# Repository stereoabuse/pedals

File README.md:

# pedals

Guitar pedal boards by stereoabuse. Each folder is a complete, separate design: netlist, board, JLCPCB fabrication files, schematic, and build notes. None has been built yet.

| Design | What it is | Enclosure |
|---|---|---|
| [preamp](preamp/) | High-gain preamp with a boost built into its first stage | 1590BB |
| [boost-preamp](boost-preamp/) | Boost and high-gain preamp as two sections in series, for the band Manat | 1590BB |
| [screamer](screamer/) | One-knob overdrive: a Tube Screamer with Drive at zero and Level at maximum, Tone only | 1590B2 |
| [muff-screamer](muff-screamer/) | Black Russian Big Muff and TS808 Tube Screamer with a series / parallel / order toggle | 1590BB |
| [decade-drive](decade-drive/) | Drive with one Level knob and twenty three-way toggles, including a tunable feedback resonator | 1590XX |

All five run from a 9 V supply or a battery.

## The two preamps

Both are derived from the Friedman BE-OD circuit (via the public PedalPCB "Thermionic Distortion" schematic).

| | [preamp](preamp/) | [boost-preamp](boost-preamp/) |
|---|---|---|
| What it is | High-gain preamp with a boost built into its first stage | Boost and high-gain preamp as two sections in series, for the band Manat |
| Footswitches | Bypass, Boost (boost only works with the preamp on) | Preamp, Boost (each works on its own) |
| Knobs | Gain, Volume, Tight, Mid, Treble, Presence | Same |
| Toggles | Depth, Clip | Depth, Clip, Voice (boost voicing) |
| Boost | Up to +12 dB above 700 Hz | Unity to +21 dB, three voicings |
| Fab files | [preamp/fab](preamp/fab/) | [boost-preamp/fab](boost-preamp/fab/) |

| preamp | boost-preamp |
|---|---|
|  |  |

## screamer

## muff-screamer

Six knobs, two footswitches, one toggle. Unlike the others, its bypass is buffered rather than true bypass.

## decade-drive

No pots except Level. Each of the twenty toggles adds a fixed part when moved up or down from centre, in weighted steps like a decade resistance box, so every setting can be written down and repeated. One row is a feedback section that resonates, scoops or drones at a tuned pitch.

`tools/jlc.py` looks up JLCPCB part stock and prices and is shared by all of them. `tools/wiring.py` draws the wiring diagram in each design's `docs/` folder.

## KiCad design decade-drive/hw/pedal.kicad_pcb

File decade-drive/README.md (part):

# decade-drive

A drive pedal with one knob and twenty three-way toggles, by stereoabuse. The idea comes from a decade resistance box: instead of turning a pot, you add fixed, weighted parts with switches, so every setting is a pattern you can write down and get back to exactly. That includes the feedback section, which can sit just under, on, or over the edge of oscillation at a tuned pitch.

Commands below are run from inside this folder. Untested hardware: the circuit is simulated and the board passes KiCad DRC, but no board has been built yet. The Feedback and Chaos rows in particular are designed from simulation and will want adjusting by ear.

## How the toggles work

Every toggle is an SPDT on-off-on with its centre lug on a circuit node. Lever up connects one extra part to that node, lever down connects a different one, centre connects nothing. With all twenty centred the pedal is its plain "home" sound: a mid-gain overdrive with a 720 Hz bass cut, soft red-LED clipping and no feedback.

Where a row has toggles numbered 9, 3 and 1 (or 3 and 1), they do the same job with those weights, like the dials of a decade box: 9 is the coarse step, 1 the fine one, and they add up.

Seen from the front:

| Row | 1 | 2 | 3 | 4 | 5 |
|---|---|---|---|---|---|
| Drive | GAIN 9 | GAIN 3 | GAIN 1 | DIODE + | DIODE - |
| Shape | BASS 3 | BASS 1 | TREBLE 3 | TREBLE 1 | CLIP |
| Feedback | SIGN | AMOUNT 3 | AMOUNT 1 | PITCH 3 | PITCH 1 |
| Chaos | SAG | GATE | OCTAVE | BLEND | BURST |

Below the grid: Level knob (left), LED and bypass footswitch (centre).

## What each toggle does

Numbers are from the simulation (see below), not measurements.

| Toggle | Up | Centre (home) | Down |
|---|---|---|---|
| GAIN 9 | +15 dB | 0 dB | -15 dB |
| GAIN 3 | +9 dB | 0 dB | -9 dB |
| GAIN 1 | +4 dB | 0 dB | -4 dB |
| DIODE + | Silicon | Red LED | Schottky |
| DIODE - | Silicon | Red LED | Schottky |
| BASS 3, BASS 1 | More bass | 720 Hz cut | Less bass |
| TREBLE 3, TREBLE 1 | Brighter | 3.4 kHz roll-off | Darker |
| CLIP | Silicon hard clipper | Off | Schottky hard clipper |
| SIGN | Regenerative: resonance, then oscillation | No feedback | Degenerative: a scoop |
| AMOUNT 3, AMOUNT 1 | More feedback | | Less feedback |
| PITCH 3 | Octave up | D | Octave down |
| PITCH 1 | Up three semitones (F) | D | Down five (A) |
| SAG | Drive op-amp on about 6.3 V | Full supply | About 5.6 V |
| GATE | Gate | Off | Soft gate |
| OCTAVE | Octave up, into the drive | Off | Rectified signal into the mix |
| BLEND | Clean, in phase | Off | Clean, out of phase |
| BURST (momentary) | Drone burst while held | | Kill while held |

Gain steps add up to 18 dB either side of home. The gain stage sits before a fixed 23 dB drive stage, so total gain runs from about 5 to 42 dB.

DIODE + and DIODE - each pick the soft-clipping diode for one half of the wave, so mixed settings clip asymmetrically. For a 0.2 V peak-to-peak input at home gain the drive stage puts out about 2.0 V peak-to-peak on LEDs, 0.9 V on silicon and 0.35 V on Schottky, so expect to move the Level knob when you change diodes.

Bass corner in Hz (the frequency below which the drive stage is fed less signal):

| BASS 3 \ BASS 1 | up | centre | down |
|---|---|---|---|
| up | 72 | 92 | 135 |
| centre | 227 | 725 | 1065 |
| down | 560 | 1790 | 2130 |

Treble corner in Hz:

| TREBLE 3 \ TREBLE 1 | up | centre | down |
|---|---|---|---|
| up | 9400 | 7900 | 3900 |
| centre | 4900 | 3400 | 1700 |
| down | 1190 | 820 | 660 |

## The Feedback row

A band-pass filter (the resonator) listens to the drive stage's output, and SIGN decides what happens to what it hears.

- SIGN up feeds it back in phase. Below a loop gain of 1 this is a resonant peak at the resonator's pitch, like a parked wah. Above 1 the pedal oscillates at that pitch: a drone.
- SIGN down feeds it back out of phase, which takes a few dB out around that pitch. This path runs through the bass filter, so the scoop is deepest with BASS up (about 10 dB) and shallow with BASS down (about 3 dB).
- AMOUNT sets the loop gain. With the THRESH trimmer at mid travel the simulated values are:

| AMOUNT 3 \ AMOUNT 1 | up | centre | down |
|---|---|---|---|
| up | 1.51 | 1.44 | 1.14 |
| centre | 1.13 | 0.79 | 0.50 |
| down | 0.49 | 0.28 | 0.23 |

So at home AMOUNT the pedal is just under the edge (a 13 dB peak), and one click of AMOUNT 1 up tips it over. THRESH scales the whole table by roughly 0.6 to 2.8, which is how you put the edge exactly where you want it.

- PITCH sets the resonator. Home is D5 (587 Hz). The nine settings are the notes of a D minor chord over three octaves: A3, D4, F4, A4, D5, F5, A5, D6, F6 (220 Hz to 1.4 kHz). PITCH 3 moves by octaves, PITCH 1 picks D, F or A. The TUNE trimmer moves all nine together, from about A4 to F5 at the home setting, so the set can be retuned to another root within that range.
- BURST up forces a drone at the current pitch while held, whatever SIGN and AMOUNT are doing. BURST down mutes the output while held.

Three things worth knowing:

1. While you play, the note holds the drive stage and the drone stays out of the way. As the note decays the drone takes over. More gain keeps the note in charge for longer. This is the simulated behaviour for a single decaying note; chords and real pickups will be messier.
2. The loop gain does not change with the GAIN, BASS or TREBLE toggles. It does drop to roughly a third with Schottky diodes selected, because they leak across the drive stage.
3. The drone runs at the drive stage's clipping level, so at full Level it is loud (about 4 V peak-to-peak on LEDs).

### Setting the two trimmers

Both are on the SMD side, reachable with the back off.

1. TUNE: centre both PITCH toggles, hold BURST up, and adjust TUNE until a tuner on the output reads D. The BP test pad carries the resonator output if you would rather measure there.
2. THRESH: SIGN up, both AMOUNT toggles centred, nothing plugged in. Turn THRESH until the drone just stops. AMOUNT 1 up should then start it again.

The intervals between PITCH settings come from part ratios and should land within about a third of a semitone of each other. The absolute pitch depends on capacitor tolerance, which is what TUNE is for.

## The Chaos row

- SAG lowers the supply of the drive op-amp only. Up clips the positive half earlier; down leaves so little headroom that the positive half is cut off almost completely. What a TL072 really does this close to its limits is not in the simulation model, so treat this one as an experiment. Each SAG position draws about 20 to 25 mA extra. The octave rectifier shares that op-amp, so OCTAVE behaves differently while SAG is engaged.
- GATE subtracts a limited copy of the signal from itself after the clipper, which cancels anything small. Up is a full gate: anything under roughly 0.1 V peak-to-peak at that point is cut by 15 dB or more, so hiss and the tail of a note go. Down cancels half as much.
- OCTAVE up full-wave rectifies the signal before the drive stage, which doubles its frequency. Down adds the half-wave rectified clean signal to the output instead; with BLEND down as well the clean part becomes fully rectified.
- BLEND adds clean signal (after the gain stage) to the output, in or out of phase with the driven signal. With OCTAVE up, the in-phase clean signal is the rectified one.

## Ordering from JLCPCB

Files are in [fab/](fab/).

1. Upload `decade-drive-revA-gerbers.zip`. Settings: 4 layers, 1.6 mm, 94 x 99.5 mm. Layer order is F, In1, In2, B (`.gtl`, `.g1`, `.g2`, `.gbl`).
2. Turn on PCB Assembly, top side.
3. Upload `decade-drive-revA-bom.csv` and `decade-drive-revA-cpl.csv`.
4. In the placement preview, check pin 1 on U1 to U6, the MOSFET (Q1), the two trimmers (RV2, RV3), and the cathode marks on the diodes and the two red LEDs (LED2, LED3). JLC's rotation convention differs from KiCad's for some packages; the CPL applies the usual corrections for SOIC and SOT-23 parts only, so this is the step to catch a mistake.

49 BOM lines, 136 placements. 2 of the lines are JLC "extended" parts (a small one-time fee each): the 1 nF NP0 capacitor and the 100k trimmer. Stock was checked on 2026-11-22.

## Parts you solder

| Part | Qty | Notes |
|---|---|---|
| Mini toggle, SPDT on-off-on | 19 | Solder lug or PC pin, 4.7 mm lug pitch |
| Mini toggle, SPDT (on)-off-(on) momentary | 1 | BURST. Same size and pitch |
| Alpha 16 mm right-angle PCB pot (RV16AF-41) | 1 | A10K |
| 3PDT latching footswitch | 1 | Wired, not board mounted |
| 3 mm LED | 1 | Any colour |
| 1/4" jack | 2 | Input must be stereo (battery switching) |
| 2.1 mm DC jack with switch lug | 1 | Panel mount, insulated |
| 9V battery snap | 1 | |
| Hammond 1590XX enclosure | 1 | 145 x 121 x 39 mm |

Toggles, pot and LED mount on the back of the board (the side with the outlines). Fit them loosely, bolt everything into the drilled enclosure, then solder, so the heights settle correctly.

The toggles stand with their lugs in a vertical line, so the levers move up and down. As designed, lever up connects the centre lug to the lower lug, which is how most mini toggles work. If one works the other way round, turn it 180 degrees.

Drill template (front view, 1:1): [docs/drill-template-1590XX.svg](docs/drill-template-1590XX.svg). Hole positions in mm from the face centre:

| Hole | x | y | dia |
|---|---|---|---|
| Toggle columns 1 to 5 | -32, -16, 0, +16, +32 | | 6.5 |
| Toggle rows Drive, Shape, Feedback, Chaos | | +31, +14, -3, -20 | 6.5 |
| LED | 0.0 | -33.0 | 3.2 |
| Level | -36.0 | -41.5 | 7.5 |
| Bypass switch | 0.0 | -53.0 | 12.5 |

The board is 94 x 99.5 mm with a notch for the footswitch. It leaves about 30 mm at the top of the face for the jacks and the DC socket. The battery lies behind the board. Check all of this against a real enclosure and real parts before drilling.

## Wiring

The diagram ([SVG](docs/wiring.svg)) shows every off-board wire.

Pads are labelled on the SMD side. Left leg in the diagram: IN, G, LED, G. Right leg: OUT, G, G, +9V.

| From | To |
|---|---|
| Input jack tip | Footswitch A2 |
| Footswitch A1 | IN |
| Footswitch B1 | OUT |
| Footswitch B2 | Output jack tip |
| Footswitch C1 | LED |
| Footswitch C2 | G (next to LED) |
| Footswitch A3 | Footswitch B3 (jumper) |
| Footswitch C3 | Footswitch A1 (grounds the board input in bypass) |
| Input jack sleeve | G (next to IN) |
| DC jack sleeve | +9V |
| DC jack centre pin | G (next to +9V) |
| Battery red | DC jack switch lug |
| Battery black | Input jack ring lug |

The output jack grounds through the metal enclosure; the spare G pad next to OUT is there if you use an insulated jack. Bypass is true bypass.

Use a regulated 9 V centre-negative supply only. Current draw is roughly 25 mA (about 50 mA with SAG engaged), so a 9 V alkaline battery should last something like 15 hours. Those figures are estimates from datasheet typicals, not measurements.

## Simulation results

From `sim/from_design.py`, which builds the SPICE deck from the board netlist and steps through the toggles:

- Home: 23.5 dB at the drive stage above the bass cut, 28 dB at the output with Level at maximum.
- Gain stage: +18 to -18 dB in 27 combinations.
- Resonator peaks, untrimmed: 220, 292, 345, 441, 584, 690, 877, 1163 and 1374 Hz, each within 30 cents of its note. TUNE moves the home pitch from 444 to 698 Hz.
- SIGN up at home AMOUNT: a 13 dB peak at 580 Hz. AMOUNT 1 down: 7 dB. AMOUNT 3 down: 4 dB.
- SIGN down: 4 dB out at 580 Hz at home AMOUNT, 6.5 dB with AMOUNT 3 up.
- Drone with no input: 581 Hz, the same on an 8.0 V and a 9.6 V supply.
- BURST starts the drone at every gain setting; KILL takes the output to zero while the drone keeps running inside.
- A decaying 147 Hz note with SIGN up, AMOUNT 3 up and GAIN 3 up: the note dominates the drive stage for the first 0.2 s, and the drone has taken over by 0.4 s.
- OCTAVE up: with a 220 Hz input the output is at 440 Hz with no 220 Hz left.
- GATE up: a 10 mV peak-to-peak input comes out 17 dB lower than ungated, 4 mV 33 dB lower, 1 mV not at all.
- SAG: 8.4, 6.3 and 5.6 V at the drive op-amp.

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
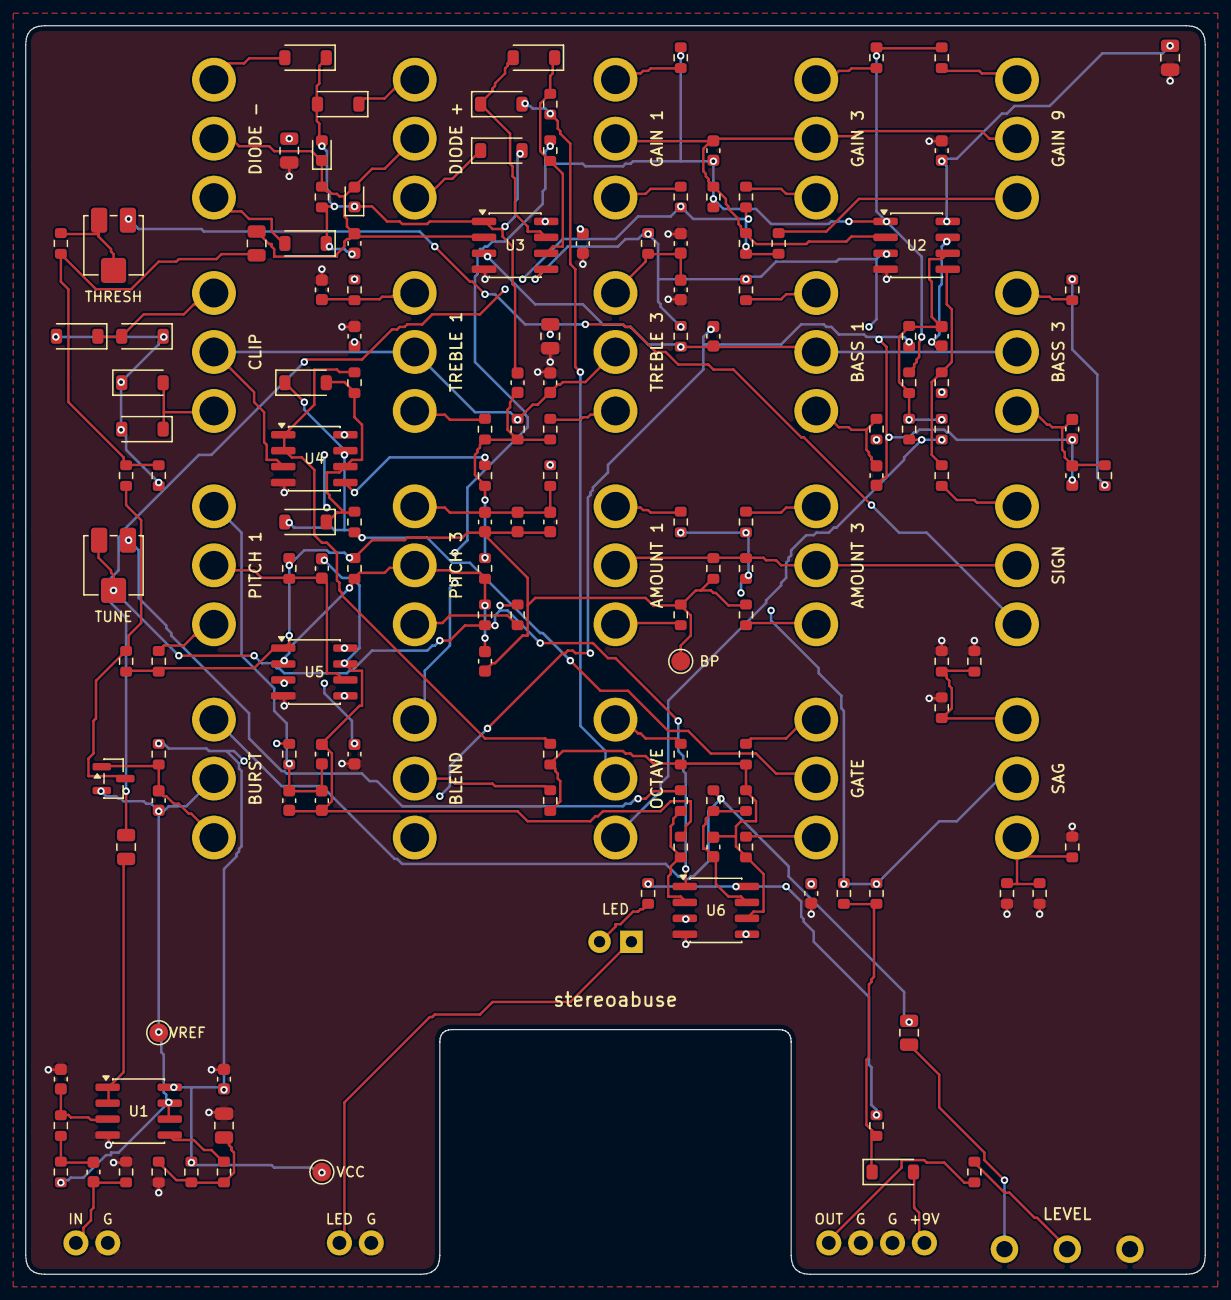
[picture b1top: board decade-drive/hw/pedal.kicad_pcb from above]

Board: 4 copper layers, 94.0 x 99.5 mm, 169 parts (1 on the bottom side), 86 nets.

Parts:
C1, C2, C3, C12, C20, C36, C37: 10u; C_0805_2012Metric
C4, C5, C6, C7, C8, C9, C10: 100n; C_0603_1608Metric
C11, C33, C35: 100p; C_0603_1608Metric
C13, C14, C19: 47p; C_0603_1608Metric
C15, C23, C34: 10n; C_0603_1608Metric
C16: 47n; C_0603_1608Metric
C17, C18: 22n; C_0603_1608Metric
C21: 1u; C_0603_1608Metric
C22, C24, C25: 4.7n; C_0603_1608Metric
C26, C27, C28, C29, C30: 1n NP0; C_0603_1608Metric
C31, C32: 330p; C_0603_1608Metric
D1: B5819W; D_SOD-123
D2, D3, D4, D6, D8, D9, D12, D13: 1N4148W; D_SOD-123
D5, D7, D10, D11: BAT54W; D_SOD-123
J_9V: +9V
J_G1, J_G2, J_G3, J_G4: GND
J_IN: IN
J_L: LED
J_OUT: OUT
LED1: LED; LED_D3.0mm
LED2, LED3: RED; LED_0603_1608Metric
Q1: 2N7002; SOT-23
R1: 22R; R_0603_1608Metric
R2, R3, R16, R17, R33: 10k; R_0603_1608Metric
R4, R7, R23, R50: 2.2k; R_0603_1608Metric
R5, R6, R38, R39: 1M; R_0603_1608Metric
R8, R9, R18, R19, R21, R22, R49, R53, R56: 4.7k; R_0603_1608Metric
R10, R11, R65, R69, R70, R71, R74: 1k; R_0603_1608Metric
R12, R13: 2.7k; R_0603_1608Metric
R14, R15: 8.2k; R_0603_1608Metric
R20, R34: 7.5k; R_0603_1608Metric
R24: 20k; R_0603_1608Metric
R25, R36, R58, R62: 22k; R_0603_1608Metric
R26, R28, R35, R37, R42, R45: 10M; R_0603_1608Metric
R27, R55, R64: 15k; R_0603_1608Metric
R29, R63: 47k; R_0603_1608Metric
R30: 150k; R_0603_1608Metric
R31: 33k; R_0603_1608Metric
R32, R57, R59, R60: 100k; R_0603_1608Metric
R40, R43: 270k; R_0603_1608Metric
R41: 91k; R_0603_1608Metric
R44: 680k; R_0603_1608Metric
R46: 120k; R_0603_1608Metric
R47: 68k; R_0603_1608Metric
R48, R52: 6.8k; R_0603_1608Metric
R51: 1.5k; R_0603_1608Metric
R54: 27k; R_0603_1608Metric
R61: 220k; R_0603_1608Metric
R66: 100R; R_0603_1608Metric
R67, R68: 220R; R_0603_1608Metric
R72, R73: 560R; R_0603_1608Metric
R75: 3.3k; R_0603_1608Metric
RV1: A10K LEVEL
RV2, RV3: 100k; Potentiometer_Bourns_3314J_Vertical
SW1: GAIN 9
SW2: GAIN 3
SW3: GAIN 1
SW4: DIODE +
SW5: DIODE -
SW6: BASS 3
SW7: BASS 1
SW8: TREBLE 3
SW9: TREBLE 1
SW10: CLIP
SW11: SIGN
SW12: AMOUNT 3
SW13: AMOUNT 1
SW14: PITCH 3
SW15: PITCH 1
SW16: SAG
SW17: GATE
SW18: OCTAVE
SW19: BLEND
SW20: BURST
TP1: VCC; TestPoint_Pad_D1.5mm
TP2: VREF; TestPoint_Pad_D1.5mm
TP3: BP; TestPoint_Pad_D1.5mm
U1, U3, U4, U5, U6: TL072; SOIC-8_3.9x4.9mm_P1.27mm
U2: NE5532; SOIC-8_3.9x4.9mm_P1.27mm

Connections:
AD1: R53.1, SW13.3
AD3: R51.1, SW12.3
AU1: R52.1, SW13.1
AU3: R50.1, SW12.1
BD1: R29.1, SW7.3
BD3: R27.1, SW6.3
BG: C34.1, Q1.1, R57.2, SW20.1
BL: R64.1, SW19.2
BU1: C18.2, R28.1, SW7.1
BU3: C16.2, C17.2, R26.1, SW6.1
BX: Q1.3, R55.2, R56.1
CA: C21.2, R32.1, R33.1, R34.2, R36.2, R38.1
CN: C19.1, C20.1, LED2.1, LED3.2, R30.1, SW4.2, SW5.2, U3.2
CNF: C20.2, R31.1, R54.2, R55.1
CO: C19.2, C21.1, D4.2, D5.2, D6.1, D7.1, LED2.2, LED3.1, R30.2, U3.1
DNS: D6.2, SW5.1
DNT: D7.2, SW5.3
DP: C15.2, R25.1, SW6.2, SW7.2, U3.3
DPS: D4.1, SW4.1
DPT: D5.1, SW4.3
FA: R48.2, R49.1, SW11.2, SW12.2, SW13.2
FJ: R54.1, RV2.2, RV2.3
FN: R24.1, SW11.3
FP: RV2.1, SW11.1
GD1: R15.1, SW3.3
GD3: R13.1, SW2.3
GD9: R11.1, SW1.3
GH: R60.1, SW17.1
GN: D12.2, D13.1, R58.2, R59.1, U4.6
GND: C1.2, C2.2, C3.2, C4.2, C5.2, C6.2, C7.2, C8.2, C9.2, C11.2, C22.2, C23.2, C24.2, C25.2, C37.2, J_G1.1, J_G2.1, J_G3.1, J_G4.1, R3.2, R5.2, R69.2, R70.2, R71.2, R72.2, R73.2, R74.2, RV1.1, U1.4, U2.4, U3.4, U4.4, U5.4, U6.4
GO: D12.1, D13.2, R59.2, SW17.2, U4.7
GS: R61.1, SW17.3
GU1: R14.2, SW3.1
GU3: R12.2, SW2.1
GU9: R10.2, SW1.1
HN: D2.1, R16.2, R17.1, U3.6
HO: D3.2, R17.2, SW18.2
HS: D8.2, D9.1, SW10.1
HT: D10.2, D11.1, SW10.3
HX: D2.2, D3.1, U3.7
IB: C12.1, U1.1, U1.2
IBC: C12.2, R8.1, R10.1, R12.1, R14.1
IN: C10.1, J_IN.1, R5.1
INA: C10.2, R6.1, R7.1
INP: C11.1, R7.2, U1.3
LA: LED1.2, R75.2
LK: J_L.1, LED1.1
LV: C36.2, RV1.3
LW: R66.1, RV1.2
MK: C36.1, R65.2, SW20.3
MN: C35.1, R20.2, R60.2, R61.2, R62.2, R63.1, R64.2, U6.6
MO: C35.2, R63.2, R65.1, U6.7
N1: C26.1, R38.2, R39.1, R40.2, SW14.2, U5.2
N2: C30.1, R43.2, SW15.2, U5.6
N3: R46.2, R47.1, U6.2
OCD: R18.1, R19.1, SW18.1
OCM: R20.1, SW18.3
OUT: J_OUT.1, R66.2
PD1: C31.1, C32.1, C33.1, R45.1, SW15.3
PD3: C27.1, C28.1, C29.1, R42.1, SW14.3
PN: C13.1, R8.2, R9.1, SW1.2, SW2.2, SW3.2, U2.2
PO: C13.2, R9.2, R11.2, R13.2, R15.2, R16.1, R21.1, SW19.3, U2.1
PU1: R44.1, SW15.1
PU3: R41.1, SW14.1
S: C14.2, C15.1, C16.1, C17.1, C18.1, R22.2, SW19.1, U2.7
SG1: R69.1, R70.1, R71.1, SW16.1
SG2: R72.1, R73.1, R74.1, SW16.3
SN: C14.1, R18.2, R19.2, R21.2, R22.1, U2.6
SP: R23.1, R24.2, U2.5
T: C22.1, R33.2, SW8.2, SW9.2, SW10.2, U4.3
TB: R58.1, R62.1, U4.1, U4.2
TD1: C25.1, R37.1, SW9.3
TD3: C23.1, C24.1, R35.1, SW8.3
TN: R47.2, RV3.1
TU1: R36.1, SW9.1
TU3: R34.1, SW8.1
V1: C26.2, C27.2, C28.2, C29.2, R39.2, R43.1, R44.2, R48.1, R50.2, R52.2, R56.2, TP3.1, U5.1
V2: C30.2, C31.2, C32.2, C33.2, R46.1, U5.7
V3: R40.1, R41.2, RV3.2, RV3.3, U6.1
V9R: D1.1, R1.1, R67.1, R68.1
VB: C3.1, R2.2, R3.1, R4.1
VBF: R4.2, U1.5
VCC: C1.1, C2.1, C4.1, C5.1, C7.1, C8.1, C9.1, R1.2, R2.1, R57.1, R75.1, TP1.1, U1.8, U2.8, U4.8, U5.8, U6.8
VIN: D1.2, J_9V.1
VREF: C34.2, D8.1, D9.2, D10.1, D11.2, Q1.2, R6.2, R23.2, R25.2, R26.2, R27.2, R28.2, R29.2, R31.2, R32.2, R35.2, R37.2, R42.2, R45.2, R49.2, R51.2, R53.2, SW20.2, TP2.1, U1.6, U1.7, U2.3, U3.5, U4.5, U5.3, U5.5, U6.3, U6.5
VS: C6.1, C37.1, R67.2, R68.2, SW16.2, U3.8

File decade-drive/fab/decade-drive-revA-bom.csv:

Comment,Designator,Footprint,LCSC Part #
10u,"C1,C2,C3,C12,C20,C36,C37",C_0805_2012Metric,C15850
100p,"C11,C33,C35",C_0603_1608Metric,C14858
47p,"C13,C14,C19",C_0603_1608Metric,C1671
10n,"C15,C23,C34",C_0603_1608Metric,C57112
47n,C16,C_0603_1608Metric,C1622
22n,"C17,C18",C_0603_1608Metric,C21122
1u,C21,C_0603_1608Metric,C15849
4.7n,"C22,C24,C25",C_0603_1608Metric,C53987
1n NP0,"C26,C27,C28,C29,C30",C_0603_1608Metric,C106246
330p,"C31,C32",C_0603_1608Metric,C1664
100n,"C4,C5,C6,C7,C8,C9,C10",C_0603_1608Metric,C14663
B5819W,D1,D_SOD-123,C8598
1N4148W,"D2,D3,D4,D6,D8,D9,D12,D13",D_SOD-123,C81598
BAT54W,"D5,D7,D10,D11",D_SOD-123,C7502705
RED,"LED2,LED3",LED_0603_1608Metric,C2286
2N7002,Q1,SOT-23,C8545
22R,R1,R_0603_1608Metric,C23345
1k,"R10,R11,R65,R69,R70,R71,R74",R_0603_1608Metric,C21190
2.7k,"R12,R13",R_0603_1608Metric,C13167
8.2k,"R14,R15",R_0603_1608Metric,C25981
10k,"R2,R3,R16,R17,R33",R_0603_1608Metric,C25804
7.5k,"R20,R34",R_0603_1608Metric,C23234
20k,R24,R_0603_1608Metric,C4184
22k,"R25,R36,R58,R62",R_0603_1608Metric,C31850
10M,"R26,R28,R35,R37,R42,R45",R_0603_1608Metric,C7250
15k,"R27,R55,R64",R_0603_1608Metric,C22809
47k,"R29,R63",R_0603_1608Metric,C25819
150k,R30,R_0603_1608Metric,C22807
33k,R31,R_0603_1608Metric,C4216
100k,"R32,R57,R59,R60",R_0603_1608Metric,C25803
2.2k,"R4,R7,R23,R50",R_0603_1608Metric,C4190
270k,"R40,R43",R_0603_1608Metric,C22965
91k,R41,R_0603_1608Metric,C23265
680k,R44,R_0603_1608Metric,C25822
120k,R46,R_0603_1608Metric,C25808
68k,R47,R_0603_1608Metric,C23231
6.8k,"R48,R52",R_0603_1608Metric,C23212
1M,"R5,R6,R38,R39",R_0603_1608Metric,C22935
1.5k,R51,R_0603_1608Metric,C22843
27k,R54,R_0603_1608Metric,C22967
220k,R61,R_0603_1608Metric,C22961
100R,R66,R_0603_1608Metric,C22775
220R,"R67,R68",R_0603_1608Metric,C22962
560R,"R72,R73",R_0603_1608Metric,C23204
3.3k,R75,R_0603_1608Metric,C22978
4.7k,"R8,R9,R18,R19,R21,R22,R49,R53,R56",R_0603_1608Metric,C23162
100k,"RV2,RV3",Potentiometer_Bourns_3314J_Vertical,C51284
TL072,"U1,U3,U4,U5,U6",SOIC-8_3.9x4.9mm_P1.27mm,C6961
NE5532,U2,SOIC-8_3.9x4.9mm_P1.27mm,C7426

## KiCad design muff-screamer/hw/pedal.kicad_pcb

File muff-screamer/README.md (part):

# muff-screamer

A black Russian Big Muff and a TS808 Tube Screamer on one board, by stereoabuse. Each has its own footswitch and its own three knobs. A toggle sets how they connect: Screamer into Muff, both in parallel, or Muff into Screamer.

Commands below are run from inside this folder. Untested hardware: the circuit is simulated and the board passes KiCad DRC, but no board has been built yet.

## What it is

| Control | Type | Notes |
|---|---|---|
| Drive | A500K pot | Screamer |
| Tone (Screamer) | W20K pot | The "TS tone" taper. B20K works but bunches the sweep at one end |
| Level | B100K pot | Screamer |
| Sustain | B100K pot | Muff |
| Tone (Muff) | B100K pot | Muff |
| Volume | B100K pot | Muff. Linear as in the original; A100K gives a smoother sweep |
| Order | SPDT on-off-on | Screamer into Muff, parallel, Muff into Screamer |
| Screamer | footswitch | Any latching switch |
| Muff | footswitch | Any latching switch |

How the two footswitches and the toggle combine:

| Toggle | Only Screamer on | Only Muff on | Both on |
|---|---|---|---|
| Screamer into Muff | Screamer | Muff | Screamer feeds the Muff |
| Parallel | Screamer | Muff | Both get the guitar, outputs are added |
| Muff into Screamer | Screamer | Muff | Muff feeds the Screamer |

Both off is bypass. The toggle only matters when both are on. In parallel the two outputs are added at full level, so both on is louder than either alone.

The Muff follows Kit Rae's trace of the V7C/V8 black Russian (bigmuffpage.com), with BC847C transistors in place of the BC547C. The Screamer is the stock TS808 circuit with a 720 Hz low cut. Two Screamer parts differ from the original and neither changes the sound: the 51 pF cap is 47 pF, and one bias resistor is 100k instead of 10k.

### Bypass is buffered, not true bypass

This is the main difference from the other pedals in this repo. Swapping the order of two true-bypass effects needs more switch poles than a toggle has, so the routing is done by three CD4053B analog switch chips, and the signal always passes through an input and an output buffer. Consequences:

- With no power (flat battery, no supply) the pedal passes no sound.
- Bypassed, the pedal is a unity-gain buffer. Simulated bypass loss is 0.2 dB or less.
- The footswitches carry no audio. Each only connects its FS pad to ground, so wiring is two wires per switch and any latching footswitch works.
- When the Muff is off its input is also disconnected, so it does not hiss or bleed into the bypassed signal.

Current draw is roughly 15 mA, so a 9 V alkaline battery should last a few tens of hours. That figure is an estimate from datasheet typicals, not a measurement.

## Ordering from JLCPCB

Files are in [fab/](fab/).

1. Upload `muff-screamer-revA-gerbers.zip`. Settings: 4 layers, 1.6 mm, 82 x 62.5 mm. Layer order is F, In1, In2, B (`.gtl`, `.g1`, `.g2`, `.gbl`).
2. Turn on PCB Assembly, top side.
3. Upload `muff-screamer-revA-bom.csv` and `muff-screamer-revA-cpl.csv`.
4. In the placement preview, check pin 1 on U1 to U7, the four transistors (Q1 to Q4), and the diode cathode bars. JLC's rotation convention differs from KiCad's for some packages; the CPL already applies the usual corrections, but this is the step to catch a mistake.

33 BOM lines, 110 placements. 4 of the lines are JLC "extended" parts (a small one-time fee each): CD4053B, BC847C, the 470 pF and the 3.9 nF capacitors. Stock was checked on 2026-11-12.

## Parts you solder

| Part | Qty | Notes |
|---|---|---|
| Alpha 16 mm right-angle PCB pot (RV16AF-41) | 6 | A500K, W20K, B100K x4 |
| Mini toggle, SPDT on-off-on | 1 | Solder lug or PC pin, 4.7 mm lug pitch |
| Latching footswitch | 2 | Wired, not board mounted. 3PDT is fine, only two lugs are used |
| 3 mm LED | 2 | Any colour |
| 1/4" jack | 2 | Input must be stereo (battery switching) |
| 2.1 mm DC jack with switch lug | 1 | Panel mount, insulated |
| 9V battery snap | 1 | |
| Hammond 1590BB enclosure | 1 | |

Pots, toggle and LEDs mount on the back of the board (the side with the pot outlines). Fit them loosely, bolt everything into the drilled enclosure, then solder, so the heights settle correctly.

Drill template (front view, 1:1): [docs/drill-template-1590BB.svg](docs/drill-template-1590BB.svg). Hole positions in mm from the face centre:

| Hole | x | y | dia |
|---|---|---|---|
| Volume (Muff) | -31.5 | +23.0 | 7.5 |
| Sustain (Muff) | -10.5 | +23.0 | 7.5 |
| Drive (Screamer) | +10.5 | +23.0 | 7.5 |
| Level (Screamer) | +31.5 | +23.0 | 7.5 |
| Order toggle | 0.0 | +1.5 | 6.5 |
| Tone (Muff) | -31.5 | -8.0 | 7.5 |
| Tone (Screamer) | +31.5 | -8.0 | 7.5 |
| Muff LED | -19.5 | -24.0 | 3.2 |
| Screamer LED | +19.5 | -24.0 | 3.2 |
| Muff switch | -27.0 | -43.0 | 12.5 |
| Screamer switch | +27.0 | -43.0 | 12.5 |

Seen from the front, the Muff is the left half (three knobs, LED, footswitch) and the Screamer is the right half. The pot, toggle and LED positions are the same as on the two preamp boards, minus two toggles, so the same drilling jig works. The battery lies between the footswitches in the board's notch. That fit is snug: check it with a real battery before drilling.

Toggle positions as designed (seen from the front): lever left is Screamer into Muff, centre is parallel, lever right is Muff into Screamer. If the switch you buy works the other way round, turn it 180 degrees.

## Wiring

The diagram ([SVG](docs/wiring.svg)) shows every off-board wire.

Pads are labelled on the SMD side. Screamer leg: IN, G, FS, G. Muff leg: FS, G, +9V, G, G, OUT.

| From | To |
|---|---|
| Input jack tip | IN |
| Input jack sleeve | G (next to IN) |
| Output jack tip | OUT |
| Screamer footswitch, one pole (common and one throw) | FS and G on the Screamer leg |
| Muff footswitch, one pole (common and one throw) | FS and G on the Muff leg |
| DC jack sleeve | +9V |
| DC jack centre pin | G (next to +9V) |
| Battery red | DC jack switch lug |
| Battery black | Input jack ring lug |

The output jack grounds through the metal enclosure; the spare G pad next to OUT is there if you use an insulated jack. Closing a footswitch turns that effect on and lights its LED.

Use a regulated 9 V centre-negative supply only.

## Simulation results

From `sim/from_design.py`, which builds the SPICE deck from the board netlist:

- All twelve combinations of toggle position and footswitch state route the signal as in the table above.
- Bypass: 0 dB, flat (0.2 dB loss in the Muff into Screamer position).
- Screamer: 15 to 35 dB of small-signal gain at 750 Hz across the Drive range, rolling off below 720 Hz.
- Muff: up to 55 dB of small-signal gain, with the usual mid scoop near 1 kHz at Tone noon.
- For a 0.2 V peak-to-peak input, the Screamer puts out up to 0.75 V and the Muff up to 1.5 V peak-to-peak with Level and Volume at maximum.

The switch chips are modelled as plain resistors, so switching pops and the chips' own distortion are not simulated.

## If something misbehaves

- Test pads: VCC should read about 8.6 V, VREF about 4.3 V.
- No sound at all: check power first, since bypass needs it.
- An LED lights but the effect does not switch: check that FS reads near 0 V with the switch closed and near VCC with it open.
- Squeal with Sustain and Drive both high and the Muff after the Screamer: that is a lot of gain in series (about 90 dB). Back off Drive or Level first.

## Schematic

[docs/schematic.pdf](docs/schematic.pdf), three sheets. It is drawn by `hw/schematic.py`, which extracts the connectivity of the drawing and refuses to write it unless every pin matches the board netlist. It is a drawing, not a KiCad schematic file.

| Sheet | Contents |
|---|---|
| [1](docs/schematic-1.png) | Power, buffers, routing switches, mixer, footswitch and toggle inputs |
| [2](docs/schematic-2.png) | Screamer |
| [3](docs/schematic-3.png) | Muff |

Regenerate with `uv run --with matplotlib python3 hw/schematic.py`.

## Scripts

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
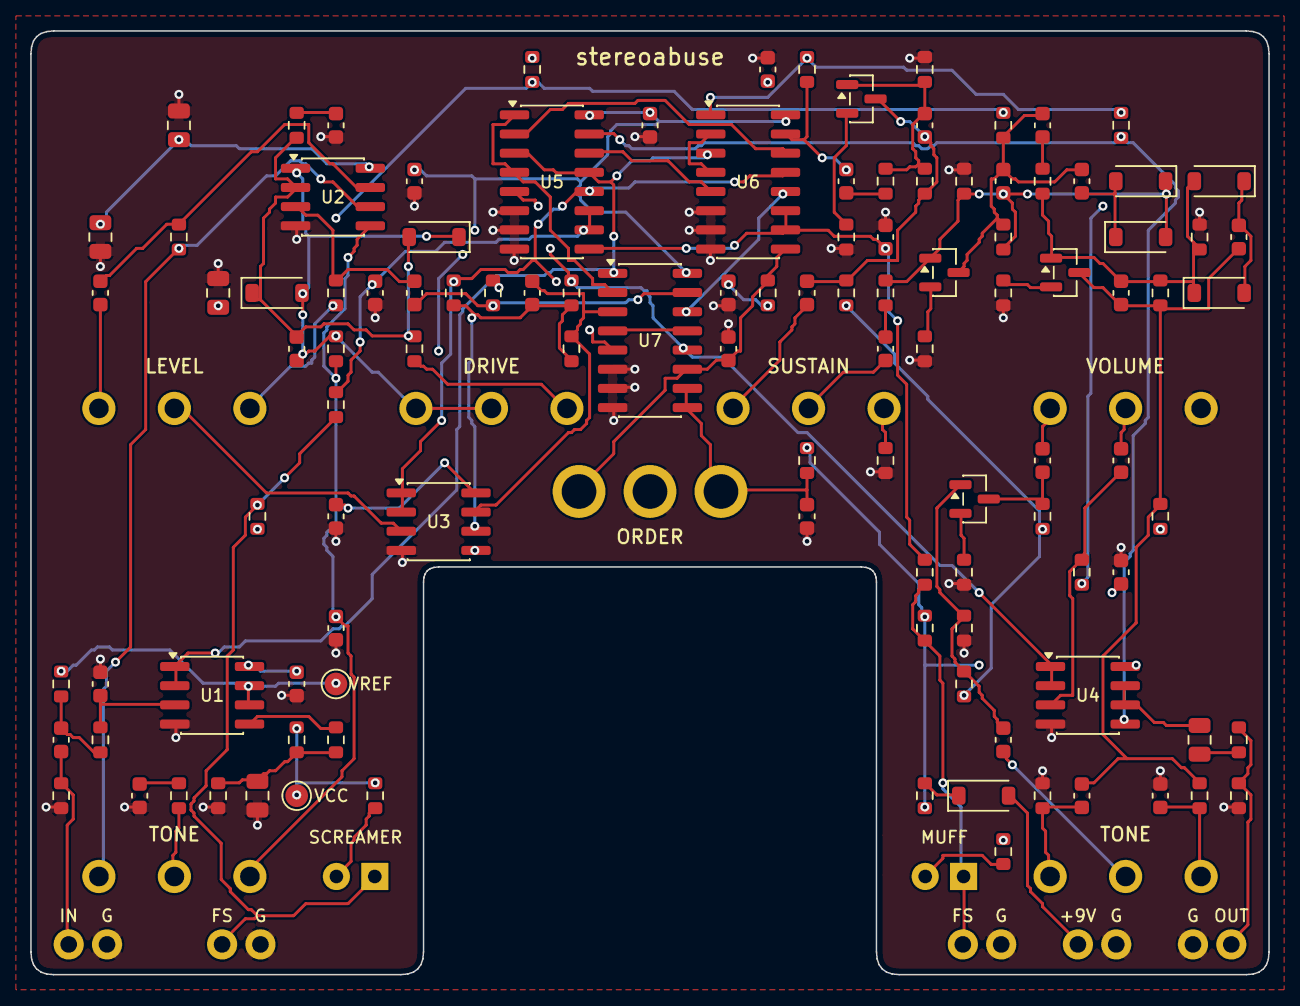
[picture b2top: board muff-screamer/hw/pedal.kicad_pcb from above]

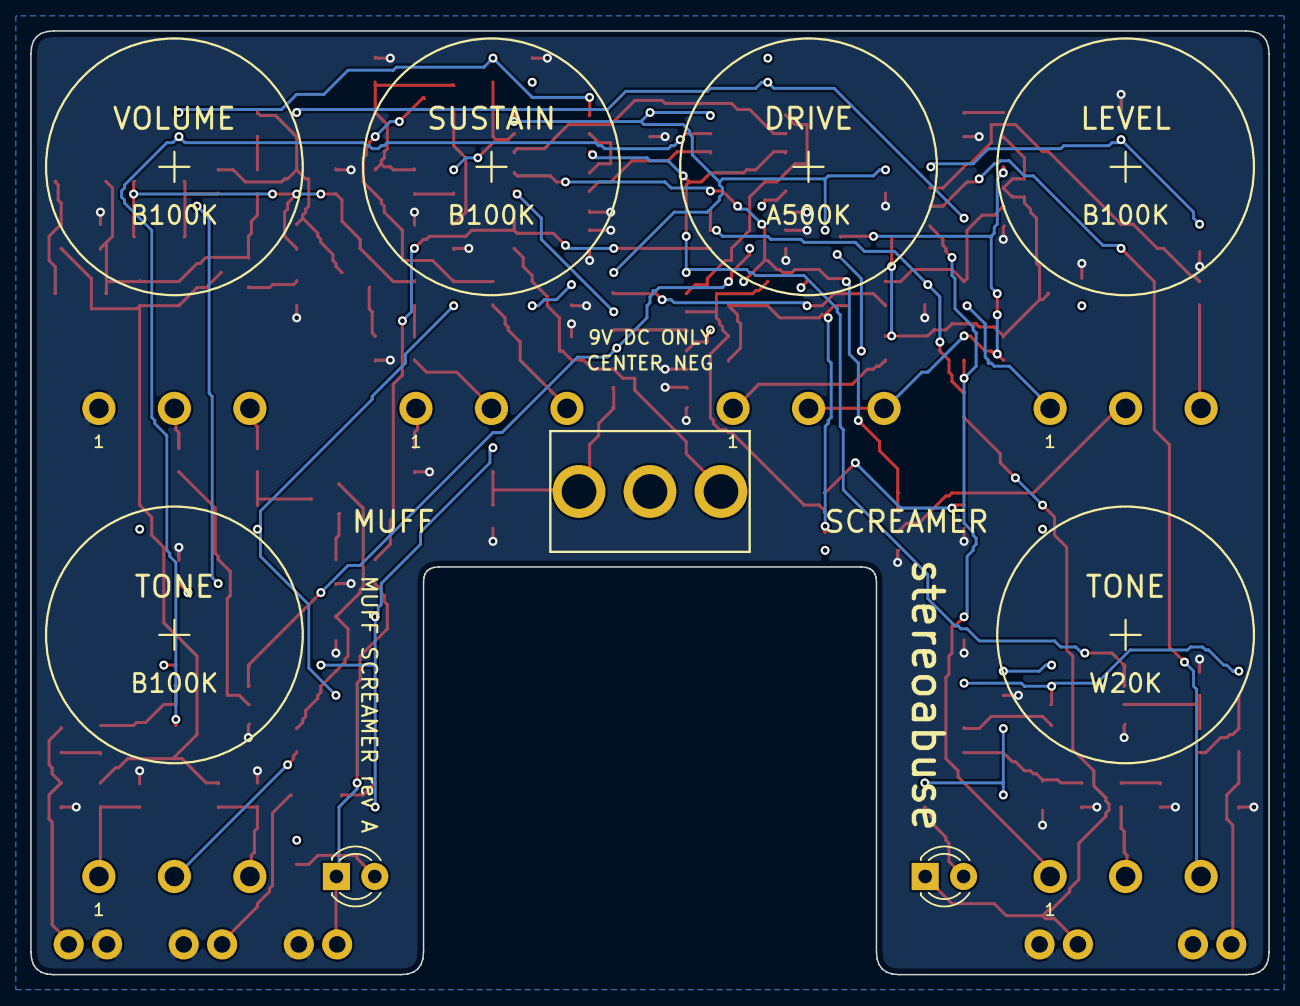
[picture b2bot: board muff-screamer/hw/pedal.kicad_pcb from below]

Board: 4 copper layers, 82.0 x 62.5 mm, 131 parts (2 on the bottom side), 74 nets.

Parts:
C1, C30, C31, C32, C33, C34, C35, C36, C50, C52, C53, C56, C61, C62, C63, C90, C91, C92, C93: 100n; C_0603_1608Metric
C2, C42: 47p; C_0603_1608Metric
C20, C21, C24, C64, C81: 10u; C_0805_2012Metric
C40, C45: 1u; C_0603_1608Metric
C41, C55, C58: 47n; C_0603_1608Metric
C43, C44: 220n; C_0603_1608Metric
C51, C54, C57: 470p; C_0603_1608Metric
C59: 3.9n; C_0603_1608Metric
C60: 10n; C_0603_1608Metric
C80: 100p; C_0603_1608Metric
D1: B5819W; D_SOD-123
D2, D3, D4, D5, D6, D7: 1N4148W; D_SOD-123
J_9V: +9V
J_FM: FS
J_FT: FS
J_G1, J_G2, J_G3, J_G4, J_G5: GND
J_IN: IN
J_OUT: OUT
LED1: SCREAMER; LED_D3.0mm
LED2: MUFF; LED_D3.0mm
Q1, Q2, Q3, Q4: BC847C; SOT-23
R1, R2, R41, R72, R83, R84: 1M; R_0603_1608Metric
R3, R21, R22, R56, R61, R70, R80, R81, R82, R91, R94: 10k; R_0603_1608Metric
R20: 22R; R_0603_1608Metric
R23: 2.2k; R_0603_1608Metric
R40, R51, R57, R62, R69, R86, R90, R93, R96, R97: 100k; R_0603_1608Metric
R42: 4.7k; R_0603_1608Metric
R43: 51k; R_0603_1608Metric
R44, R45, R55: 1k; R_0603_1608Metric
R46: 220R; R_0603_1608Metric
R50: 39k; R_0603_1608Metric
R52, R58, R63, R68: 470k; R_0603_1608Metric
R53, R59, R64: 12k; R_0603_1608Metric
R54, R60, R65: 390R; R_0603_1608Metric
R66: 22k; R_0603_1608Metric
R67: 20k; R_0603_1608Metric
R71: 2.7k; R_0603_1608Metric
R73, R85: 100R; R_0603_1608Metric
R92, R95: 3.3k; R_0603_1608Metric
RV1: A500K DRIVE
RV2: W20K TONE
RV3: B100K LEVEL
RV4: B100K SUSTAIN
RV5: B100K TONE
RV6: B100K VOLUME
SW1: ORDER
TP1: VCC; TestPoint_Pad_D1.5mm
TP2: VREF; TestPoint_Pad_D1.5mm
U1, U2, U3, U4: TL072; SOIC-8_3.9x4.9mm_P1.27mm
U5, U6, U7: CD4053B; SOIC-16_3.9x9.9mm_P1.27mm

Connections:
CN: C42.1, D2.2, D3.1, R42.1, R43.1, U2.2
CO: C42.2, D2.1, D3.2, R44.1, RV1.2, RV1.3, U2.1
CP: C40.2, R40.1, U2.3
D2X: C55.2, D4.2, D5.1
D3X: C58.2, D6.2, D7.1
DR: R43.2, RV1.1
FM: J_FM.1, LED2.1, R93.2, R94.1
FT: J_FT.1, LED1.1, R90.2, R91.1
GND: C2.2, C20.2, C21.2, C24.2, C30.2, C31.2, C32.2, C33.2, C34.2, C35.2, C36.2, C41.2, C43.2, C44.2, C60.2, C64.2, C90.2, C91.2, C92.2, C93.2, J_G1.1, J_G2.1, J_G3.1, J_G4.1, J_G5.1, R1.2, R22.2, R51.2, R54.2, R55.2, R57.2, R60.2, R62.2, R65.2, R66.2, R69.2, R71.2, R86.2, RV6.1, SW1.2, U1.4, U2.4, U3.4, U4.4, U5.6, U5.7, U5.8, U6.6, U6.7, U6.8, U7.6, U7.7, U7.8
IB: U1.1, U1.2, U5.3, U5.13, U6.3, U7.1
IN: C1.1, J_IN.1, R1.1
INA: C1.2, R2.1, R3.1
INP: C2.1, R3.2, U1.3
LA1: LED1.2, R92.2
LA2: LED2.2, R95.2
LV: C45.2, RV3.3
LW: RV3.2, U3.3
MA: C50.2, R50.1
MBP: C63.2, R72.1, U4.3
MFI: C50.1, R84.1, U6.15
MFO: R81.1, U4.1, U4.2, U5.5, U7.12
MFS: U6.2, U6.4
MIX: C80.2, R82.2, U3.7, U7.3
MN: C80.1, R80.2, R81.2, R82.1, U3.6
MTW: C61.1, RV5.2
MV: C62.2, RV6.3
MVW: C63.1, RV6.2
NAB: C92.1, R96.2, SW1.1, U6.9, U7.11
NBA: C93.1, R97.2, SW1.3, U7.9, U7.10
NMF: C91.1, R94.2, U5.9, U6.10, U6.11
NTS: C90.1, R91.2, U5.10, U5.11
OB: C81.1, U4.6, U4.7
OC: C81.2, R85.1
OSEL: R83.1, U4.5, U5.15
OUT: J_OUT.1, R85.2, R86.1
Q1B: C51.2, Q1.1, R50.2, R51.1, R52.2
Q1C: C51.1, C52.1, Q1.3, R52.1, R53.2
Q1E: Q1.2, R54.1
Q2A: C53.2, R56.1
Q2B: C54.2, D4.1, D5.2, Q2.1, R56.2, R57.1, R58.2
Q2C: C54.1, C55.1, C56.1, Q2.3, R58.1, R59.2
Q2E: Q2.2, R60.1
Q3A: C56.2, R61.1
Q3B: C57.2, D6.1, D7.2, Q3.1, R61.2, R62.1, R63.2
Q3C: C57.1, C58.1, C59.1, Q3.3, R63.1, R64.2, R67.1
Q3E: Q3.2, R65.1
Q4B: C61.2, Q4.1, R68.2, R69.1
Q4C: C62.1, Q4.3, R70.2
Q4E: Q4.2, R71.1
RG: C41.1, R42.2
SU1: R55.1, RV4.1
SU3: C52.2, RV4.3
SUW: C53.1, RV4.2
T1: C43.1, R44.2, RV2.1, U2.5
TH: C59.2, R66.1, RV5.3
TL: C60.1, R67.2, RV5.1
TN: R45.1, RV2.3, U2.6
TO: C45.1, R45.2, U2.7
TSI: C40.1, R41.1, U7.15
TSO: R80.1, U3.1, U3.2, U5.12, U6.13, U7.5
TW: R46.1, RV2.2
TX: C44.1, R46.2
V9R: D1.1, R20.1
VB: C24.1, R21.2, R22.1, R23.1
VBF: R23.2, U1.5
VCC: C20.1, C21.1, C30.1, C31.1, C32.1, C33.1, C34.1, C35.1, C36.1, R20.2, R21.1, R73.1, R90.1, R92.1, R93.1, R95.1, R96.1, R97.1, TP1.1, U1.8, U2.8, U3.8, U4.8, U5.16, U6.16, U7.16
VIN: D1.2, J_9V.1
VM: C64.1, R53.1, R59.1, R64.1, R68.1, R70.1, R73.2
VREF: R2.2, R40.2, R41.2, R72.2, R83.2, R84.2, RV3.1, TP2.1, U1.6, U1.7, U3.5, U6.1
W: U6.12, U7.14
W2: U7.4, U7.13
XMF: U5.1, U5.4, U7.2
XTS: U5.14, U6.5
YSA: U5.2, U6.14

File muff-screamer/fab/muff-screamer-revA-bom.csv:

Comment,Designator,Footprint,LCSC Part #
47p,"C2,C42",C_0603_1608Metric,C1671
10u,"C20,C21,C24,C64,C81",C_0805_2012Metric,C15850
100n,"C1,C30,C31,C32,C33,C34,C35,C36,C50,C52,C53,C56,C61,C62,C63,C90,C91,C92,C93",C_0603_1608Metric,C14663
1u,"C40,C45",C_0603_1608Metric,C15849
47n,"C41,C55,C58",C_0603_1608Metric,C1622
220n,"C43,C44",C_0603_1608Metric,C21120
470p,"C51,C54,C57",C_0603_1608Metric,C106211
3.9n,C59,C_0603_1608Metric,C1618
10n,C60,C_0603_1608Metric,C57112
100p,C80,C_0603_1608Metric,C14858
B5819W,D1,D_SOD-123,C8598
1N4148W,"D2,D3,D4,D5,D6,D7",D_SOD-123,C81598
BC847C,"Q1,Q2,Q3,Q4",SOT-23,C8664
1M,"R1,R2,R41,R72,R83,R84",R_0603_1608Metric,C22935
22R,R20,R_0603_1608Metric,C23345
10k,"R3,R21,R22,R56,R61,R70,R80,R81,R82,R91,R94",R_0603_1608Metric,C25804
2.2k,R23,R_0603_1608Metric,C4190
4.7k,R42,R_0603_1608Metric,C23162
51k,R43,R_0603_1608Metric,C23196
1k,"R44,R45,R55",R_0603_1608Metric,C21190
220R,R46,R_0603_1608Metric,C22962
39k,R50,R_0603_1608Metric,C23153
470k,"R52,R58,R63,R68",R_0603_1608Metric,C23178
12k,"R53,R59,R64",R_0603_1608Metric,C22790
390R,"R54,R60,R65",R_0603_1608Metric,C23151
22k,R66,R_0603_1608Metric,C31850
20k,R67,R_0603_1608Metric,C4184
2.7k,R71,R_0603_1608Metric,C13167
100R,"R73,R85",R_0603_1608Metric,C22775
100k,"R40,R51,R57,R62,R69,R86,R90,R93,R96,R97",R_0603_1608Metric,C25803
3.3k,"R92,R95",R_0603_1608Metric,C22978
TL072,"U1,U2,U3,U4",SOIC-8_3.9x4.9mm_P1.27mm,C6961
CD4053B,"U5,U6,U7",SOIC-16_3.9x9.9mm_P1.27mm,C6742

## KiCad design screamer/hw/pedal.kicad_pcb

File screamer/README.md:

# screamer

One-knob overdrive by stereoabuse: a Tube Screamer with Drive fixed at zero and Level fixed at maximum, so the only control is Tone. It is meant as an always-ready tightening boost in front of an amp that is already distorting. Sibling designs are in [../preamp](../preamp) and [../boost-preamp](../boost-preamp). Commands below are run from inside this folder.

Rev A. Untested hardware: the circuit is simulated and the board passes KiCad DRC, but no board has been built yet.

## What it is

| Control | Type | Notes |
|---|---|---|
| Tone | W20K pot | The stock Tube Screamer tone control |
| Bypass | 3PDT footswitch | True bypass, wired by hand |

The voicing sits halfway between a stock Tube Screamer and a tightened one. Simulated gain in dB with Tone at noon:

| | 80 Hz | 300 Hz | 750 Hz | 2.5 kHz |
|---|---|---|---|---|
| Stock Tube Screamer | +3.7 | +12.5 | +15.7 | +10.6 |
| This pedal | +5.4 | +13.8 | +17.4 | +13.0 |

- The bass cut starts near 850 Hz (stock is 720 Hz).
- The output is about 2.5 dB hotter than a stock pedal with Level at maximum.
- The clipping diodes are stock, so it still clips lightly on hard picking, as a Tube Screamer does at zero Drive.
- Two op-amp followers replace the transistor buffers of the original.
- It runs on 9 V only (battery or supply). There is no charge pump.

## Ordering from JLCPCB

Files are in [fab/](fab/).

1. Upload `screamer-revA-gerbers.zip`. Settings: 4 layers, 1.6 mm, 34 x 42 mm. Layer order is F, In1, In2, B (`.gtl`, `.g1`, `.g2`, `.gbl`).
2. Turn on PCB Assembly, top side.
3. Upload `screamer-revA-bom.csv` and `screamer-revA-cpl.csv`.
4. In the placement preview, check pin 1 on U1 and U2 and the cathode bars on D1, D2, D3. The CPL applies the usual rotation corrections, but this is the step to catch a mistake.

21 BOM lines, 35 placements, all from JLC's basic library (no extended-part fees). Stock was checked on 2026-11-12.

## Parts you solder

| Part | Qty | Notes |
|---|---|---|
| Alpha 16 mm right-angle PCB pot (RV16AF-41), W20K | 1 | Sold as "20K W" or "TS tone" taper. B20K or B25K also works, but then nearly all the change happens in the last quarter turn |
| 3PDT footswitch | 1 | Wired, not board mounted |
| 3 mm LED | 1 | Any colour |
| 1/4" jack | 2 | Input must be stereo (battery switching) |
| 2.1 mm DC jack with switch lug | 1 | Panel mount, insulated |
| 9V battery snap | 1 | |
| Hammond 1590B2 enclosure | 1 | The tall version of the 1590B, 33.5 mm inside |

The pot and LED mount on the back of the board (the side with the pot outline). The pot is the only thing holding the board, which is fine at this size.

## Enclosure layout

Drill template (front view, 1:1): [docs/drill-template-1590B2.svg](docs/drill-template-1590B2.svg). Hole positions in mm from the face centre:

| Hole | x | y | dia |
|---|---|---|---|
| Tone | 0.0 | +10.0 | 7.5 |
| LED | 0.0 | -14.5 | 3.2 |
| Footswitch | 0.0 | -40.0 | 12.5 |

Jacks and the DC socket go on the top end wall: a jack about 19 mm either side of centre and the DC socket in the centre. Mark those from the parts you buy.

The battery lies flat behind the board, between the board and the back plate, with its snap end toward the jacks. How the depth adds up:

| Layer | Depth |
|---|---|
| Face to board (pot body) | about 10.7 mm |
| Board | 1.6 mm |
| Tallest SMD part | about 1.8 mm |
| Battery | 17.5 mm |
| Total | about 31.6 mm of the 33.5 mm available |

A 9V battery has a metal case and it rests against the populated side of the board. Put a layer of insulating tape or thin foam between them.

The footswitch is not on the board. A footswitch body is 13 to 17 mm deep and the pot holds the board about 11 mm behind the face, so the two cannot share one flat board.

## Wiring

The diagram ([SVG](docs/wiring.svg)) shows every off-board wire. The tables below list the same connections lug by lug.

Pads are labelled on the SMD side. Top edge: +9V, G on one corner and a spare G on the other. Bottom edge: IN, G, LED, G, OUT.

Footswitch (3PDT, columns A B C, row 2 is the common):

| Lug | Goes to |
|---|---|
| A1 | board IN |
| A2 | input jack tip |
| A3 | wire to B3 |
| B1 | board OUT |
| B2 | output jack tip |
| C1 | board LED |
| C2 | board G |
| C3 | board IN (grounds the input when bypassed) |

Power: DC jack centre pin to G, DC jack sleeve to +9V, battery red to the DC jack switch lug, battery black to the input jack ring lug, input jack sleeve to G.

Use a 9 V centre-negative supply. The op-amps are rated well above that, but the 10 uF capacitors are 25 V parts, so do not go above 18 V.

Test pads: 9V should read about 8.7 V and VREF about half that.

## How the board was made

Everything is generated from [hw/design.py](hw/design.py), which holds the full netlist with JLC part numbers.

Schematic: [docs/schematic.pdf](docs/schematic.pdf) ([image](docs/schematic-1.png)). It is drawn by `hw/schematic.py`, which refuses to write the drawing unless every pin matches the board netlist. Regenerate with `uv run --with matplotlib python3 hw/schematic.py`.

| Step | Script |
|---|---|
| Simulate the netlist in ngspice | `sim/from_design.py` |
| Draw and verify the schematic | `hw/schematic.py` |
| Place parts | `hw/place.py` |
| Build the KiCad board | `hw/build_pcb.py` |
| Route (own grid router) | `hw/route.py` |
| Apply tracks, fill planes, DRC | `hw/apply_routes.py`, `hw/drc.sh` |
| Gerbers, BOM, CPL, renders | `hw/export.py` |
| Drill template | `hw/drill_template.py` |

`hw/make.sh` runs place through DRC. The board file is [hw/pedal.kicad_pcb](hw/pedal.kicad_pcb).

## Things to check before paying or drilling

1. Open `hw/pedal.kicad_pcb` in KiCad and look it over.
2. The depth stack above. The pot height (10.7 mm) is from the Alpha drawing as modelled for the other two boards; measure your pot. There is about 2 mm to spare.
3. Top-mounted jacks in a 60 mm wide box are tight. Check that your two jacks and the DC socket fit side by side, and that the jacks do not reach down as far as the battery (it ends about 32 mm below the inside of the top wall).
4. Pot footprint: 3 pins at 5.0 mm pitch, 16 mm below the shaft.
5. The simulation uses a linear tone pot, so the tone sweep with the W taper is not modelled.

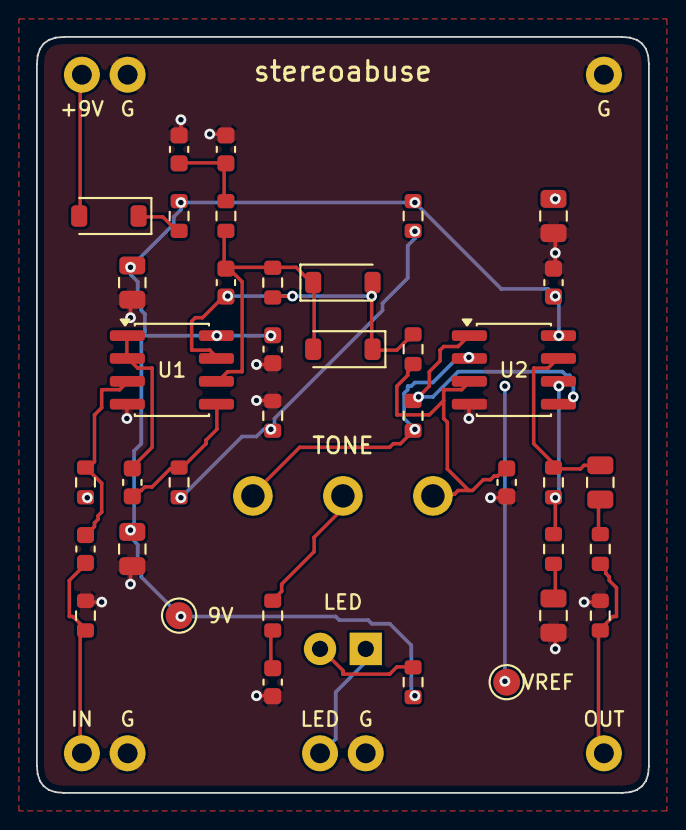
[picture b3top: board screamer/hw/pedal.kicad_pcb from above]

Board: 4 copper layers, 34.0 x 42.0 mm, 47 parts (1 on the bottom side), 24 nets.

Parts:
C1: 22n; C_0603_1608Metric
C3: 1u; C_0603_1608Metric
C4: 33n; C_0603_1608Metric
C4B: 6.8n; C_0603_1608Metric
C5: 47p; C_0603_1608Metric
C6, C7: 220n; C_0603_1608Metric
C8, C9, C20, C21, C24: 10u; C_0805_2012Metric
C22, C23: 100n; C_0603_1608Metric
D1: B5819W; D_SOD-123
D2, D3: 1N4148W; D_SOD-123
J_9V: +9V
J_G1, J_G2, J_G3, J_G4: GND
J_IN: IN
J_L: LED
J_OUT: OUT
LED1: LED; LED_D3.0mm
R1: 1M; R_0603_1608Metric
R2: 510k; R_0603_1608Metric
R3, R10, R12, R21, R22: 10k; R_0603_1608Metric
R4: 4.7k; R_0603_1608Metric
R5: 51k; R_0603_1608Metric
R6, R7: 1k; R_0603_1608Metric
R8: 220R; R_0603_1608Metric
R9, R13: 3.3k; R_0603_1608Metric
R11: 100R; R_0603_1608Metric
R20: 22R; R_0603_1608Metric
RV1: W20K TONE
TP1: 9V; TestPoint_Pad_D1.5mm
TP2: VREF; TestPoint_Pad_D1.5mm
U1, U2: TL072; SOIC-8_3.9x4.9mm_P1.27mm

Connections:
B1: C3.1, U1.1, U1.2
CN: C5.1, D2.2, D3.1, R4.1, R5.1, U1.6
CO: C5.2, D2.1, D3.2, R5.2, R6.1, U1.7
CP: C3.2, R3.1, U1.5
GND: C4.2, C4B.2, C6.2, C7.2, C8.2, C20.2, C21.2, C22.2, C23.2, C24.2, J_G1.1, J_G2.1, J_G3.1, J_G4.1, R1.2, R12.2, R22.2, U1.4, U2.4
IN: C1.1, J_IN.1, R1.1
LA: LED1.2, R13.2
LK: J_L.1, LED1.1
NA: C1.2, R2.1, U1.3
OC: C9.2, R11.1
OG: C8.1, R10.2
ON: R9.1, R10.1, U2.6
OUT: J_OUT.1, R11.2, R12.1
OUTA: C9.1, R9.2, U2.7
RG: C4.1, C4B.1, R4.2
T1: C6.1, R6.2, RV1.1, U2.3
TN: R7.1, RV1.3, U2.2
TO: R7.2, U2.1, U2.5
TW: R8.1, RV1.2
TX: C7.1, R8.2
V9: C20.1, C21.1, C22.1, C23.1, R13.1, R20.2, R21.1, TP1.1, U1.8, U2.8
V9R: D1.1, R20.1
VIN: D1.2, J_9V.1
VREF: C24.1, R2.2, R3.2, R21.2, R22.1, TP2.1

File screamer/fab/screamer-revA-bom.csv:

Comment,Designator,Footprint,LCSC Part #
22n,C1,C_0603_1608Metric,C21122
10u,"C8,C9,C20,C21,C24",C_0805_2012Metric,C15850
100n,"C22,C23",C_0603_1608Metric,C14663
1u,C3,C_0603_1608Metric,C15849
33n,C4,C_0603_1608Metric,C21117
6.8n,C4B,C_0603_1608Metric,C1631
47p,C5,C_0603_1608Metric,C1671
220n,"C6,C7",C_0603_1608Metric,C21120
B5819W,D1,D_SOD-123,C8598
1N4148W,"D2,D3",D_SOD-123,C81598
1M,R1,R_0603_1608Metric,C22935
100R,R11,R_0603_1608Metric,C22775
510k,R2,R_0603_1608Metric,C23192
22R,R20,R_0603_1608Metric,C23345
10k,"R3,R10,R12,R21,R22",R_0603_1608Metric,C25804
4.7k,R4,R_0603_1608Metric,C23162
51k,R5,R_0603_1608Metric,C23196
1k,"R6,R7",R_0603_1608Metric,C21190
220R,R8,R_0603_1608Metric,C22962
3.3k,"R9,R13",R_0603_1608Metric,C22978
TL072,"U1,U2",SOIC-8_3.9x4.9mm_P1.27mm,C6961
